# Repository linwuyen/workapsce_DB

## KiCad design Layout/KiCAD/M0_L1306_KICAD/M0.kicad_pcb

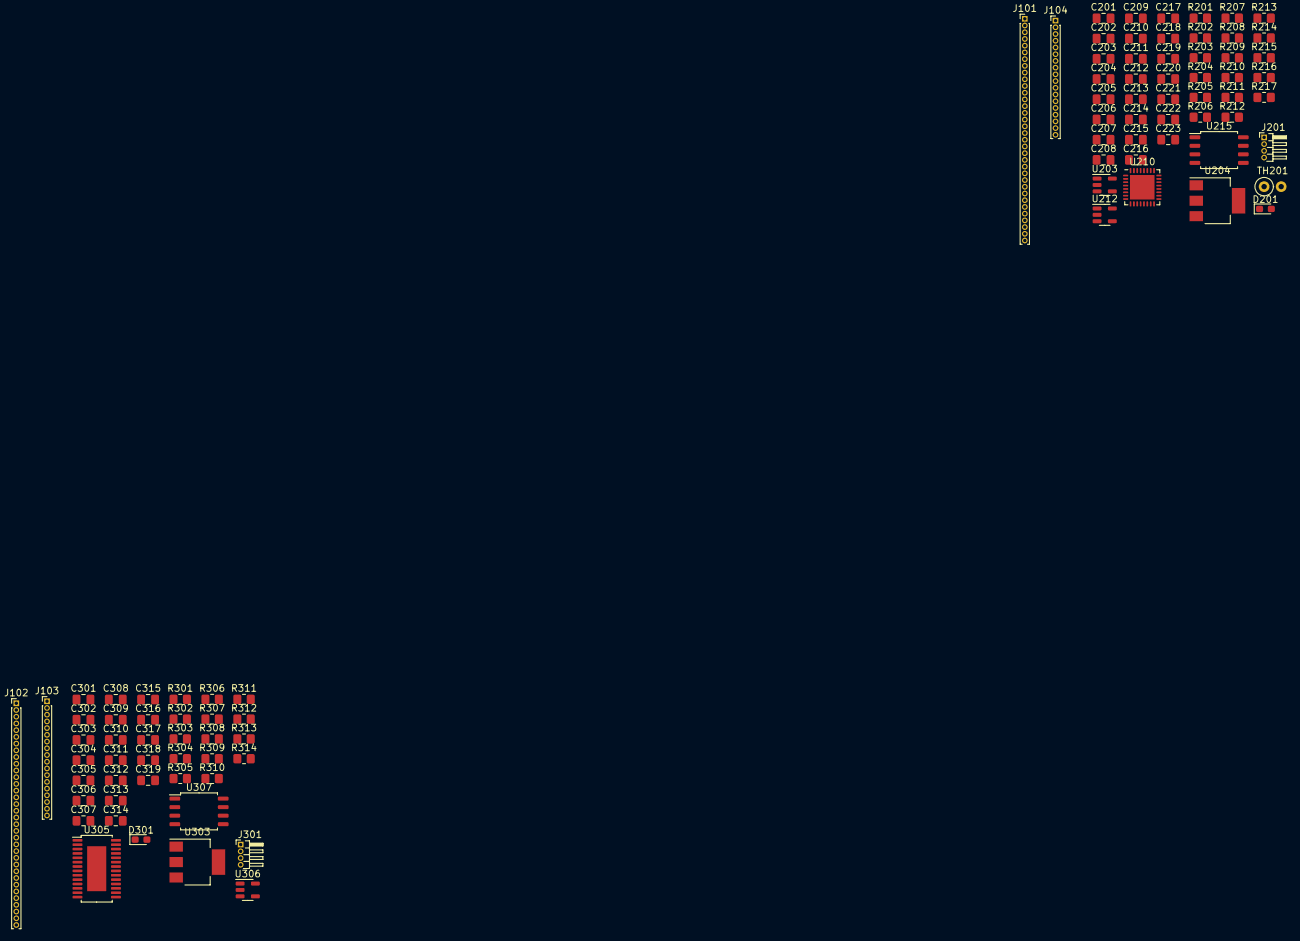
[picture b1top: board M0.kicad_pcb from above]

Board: 2 copper layers, 91 parts (0 on the bottom side), 93 nets, no tracks yet.

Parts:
C201, C207, C218, C219, C221, C304, C311, C312, C318: 10nF; C_0805_2012Metric_Pad1.18x1.45mm_HandSolder
C202, C203, C301, C303: 4.7uF; C_0805_2012Metric_Pad1.18x1.45mm_HandSolder
C204, C216, C319: 0.47uF; C_0805_2012Metric_Pad1.18x1.45mm_HandSolder
C205, C210, C213, C217, C220, C223, C305, C306, C310, C315, C317: 100nF; C_0805_2012Metric_Pad1.18x1.45mm_HandSolder
C206, C209, C211, C222, C302, C307, C308, C316: 100pF; C_0805_2012Metric_Pad1.18x1.45mm_HandSolder
C208, C212, C309: 10uF; C_0805_2012Metric_Pad1.18x1.45mm_HandSolder
C214, C215, C313, C314: 18pF; C_0805_2012Metric_Pad1.18x1.45mm_HandSolder
D201, D301: LED; LED_0603_1608Metric_Pad1.05x0.95mm_HandSolder
J101, J102: Conn_01x34_Socket; PinHeader_1x34_P1.00mm_Vertical
J103, J104: Conn_01x18_Pin; PinHeader_1x18_P1.00mm_Vertical
J201, J301: SWD_01x04_Pin; PinHeader_1x04_P1.00mm_Horizontal
R201, R214, R311: 4.7k; R_0805_2012Metric_Pad1.20x1.40mm_HandSolder
R202, R203, R207, R208, R209, R302, R303, R307, R313, R314: 22R; R_0805_2012Metric_Pad1.20x1.40mm_HandSolder
R204, R205, R216, R301, R304: 10k; R_0805_2012Metric_Pad1.20x1.40mm_HandSolder
R206, R210, R211, R305, R309, R310: 2.2k; R_0805_2012Metric_Pad1.20x1.40mm_HandSolder
R212: 100k; R_0805_2012Metric_Pad1.20x1.40mm_HandSolder
R213, R215, R306, R308: 10R; R_0805_2012Metric_Pad1.20x1.40mm_HandSolder
R217, R312: 100R; R_0805_2012Metric_Pad1.20x1.40mm_HandSolder
TH201: Thermistor_NTC_5K; R_Axial_DIN0207_L6.3mm_D2.5mm_P2.54mm_Vertical
U203, U212, U306: SN74LVC1G08; SOT-23-5
U204, U303: LM1117MP-3.3; SOT-223-3_TabPin2
U210: MSPM0L1306; QFN-32-1EP_5x5mm_P0.5mm_EP3.65x3.65mm
U215, U307: TL082; SOIC-8_5.275x5.275mm_P1.27mm
U305: M0A23EC1AC; TSSOP-28-1EP_4.4x9.7mm_P0.65mm_EP2.85x6.7mm

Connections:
+3.3V: C306.1, C309.1, C310.1, C315.2, C317.2, C319.1, J301.1, R301.1, U303.2 (VO), U305.1 (VDD), U306.5 (VCC), U307.8 (V+)
+3.3VP: C204.1, C208.1, C210.1, C212.1, C213.1, C217.1, C220.1, C223.1, J201.1, R204.2, R205.1, R206.1, R210.1, R211.1, R216.1, U203.5 (VCC), U204.2 (VO), U210.4 (VDD), U212.5 (VCC), U215.8 (V+)
/Nunoton_M0A23EC1AC/5V: C301.1, C303.1, C305.1, U303.3 (VI)
/Nunoton_M0A23EC1AC/ACMP0: J103.4, U305.23 (PC.1)
/Nunoton_M0A23EC1AC/ADC12: J103.5, R312.1
/Nunoton_M0A23EC1AC/DAC 1: C318.1, J103.3, R311.1
/Nunoton_M0A23EC1AC/GND: C301.2, C303.2, C305.2, C309.2, C310.2, U303.1 (GND)
/Nunoton_M0A23EC1AC/MCU_TX: C312.1, R308.2
/Nunoton_M0A23EC1AC/PD.1: J103.10, U305.9 (PD.1)
/Nunoton_M0A23EC1AC/PD.2: J103.11, U305.10 (PD.2)
/Nunoton_M0A23EC1AC/PD.3: J103.12, U305.11 (PD.3)
/Nunoton_M0A23EC1AC/PD.5: J103.13, U305.18 (PD.5)
/Nunoton_M0A23EC1AC/PD.6: U305.19 (PD.6), U305.20 (PD.7)
/Nunoton_M0A23EC1AC/PICO: C308.1, R307.2
/Nunoton_M0A23EC1AC/POCI: C307.1, R303.2
/Nunoton_M0A23EC1AC/PWM_BRAKE1: J103.2, U305.25 (PA.2)
/Nunoton_M0A23EC1AC/PWM_CH0: J103.1, R311.2, U306.4
/Nunoton_M0A23EC1AC/SCL: C313.1, R309.2, U305.14 (PB.7)
/Nunoton_M0A23EC1AC/SCLK: C302.1, R302.2
/Nunoton_M0A23EC1AC/SDA: C314.1, R310.2, U305.16 (PB.5)
/Nunoton_M0A23EC1AC/TM0: J103.8, U305.17 (PD.4)
/Nunoton_M0A23EC1AC/TM0_EXT: J103.7, U305.22 (PC.2)
/TI_MSPM0L1306/+5VP: C202.1, C203.1, C205.1, U204.3 (VI)
/TI_MSPM0L1306/ADC12: J104.12, R217.1
/TI_MSPM0L1306/CAPTURE_0: J104.3, U210.11 (PA7)
/TI_MSPM0L1306/COMPARE_0: J104.4, U210.9 (PA5)
/TI_MSPM0L1306/DAC 1: C201.1, J104.6, R201.2
/TI_MSPM0L1306/DAC 2: C219.1, J104.10, R214.1
/TI_MSPM0L1306/GND: C202.2, C203.2, C205.2, C208.2, C210.2, U204.1 (GND)
/TI_MSPM0L1306/OPA1.IN0+: J104.8, R216.2, TH201.1, U210.22 (PA18/A7)
/TI_MSPM0L1306/OPA1.IN1-: J104.7, U210.21 (PA17)
/TI_MSPM0L1306/OPA1.OUT: J104.9, U210.20 (PA16/A8)
/TI_MSPM0L1306/PA1: J104.13, U210.2 (PA1)
/TI_MSPM0L1306/PA12: J104.14, U210.16 (PA12)
/TI_MSPM0L1306/PA13: J104.15, U210.17 (PA13)
/TI_MSPM0L1306/PA14: J104.16, U210.18 (PA14)
/TI_MSPM0L1306/PA15: J104.17, U210.19 (PA15/A9)
/TI_MSPM0L1306/PA24: J104.18, U210.28 (PA24/A3)
/TI_MSPM0L1306/PICO: C211.1, R209.2
/TI_MSPM0L1306/POCI: C206.1, R207.2
/TI_MSPM0L1306/PWM 1: J104.5, R201.1, U203.4
/TI_MSPM0L1306/PWM 2: J104.11, R214.2, U212.4
/TI_MSPM0L1306/SCL: C215.1, R211.2, U210.15 (PA11)
/TI_MSPM0L1306/SCLK: C209.1, R208.2
/TI_MSPM0L1306/SDA: C214.1, R210.2, U210.14 (PA10)
/TI_MSPM0L1306/TX: C218.1, R213.1
/TI_MSPM0L1306/VREF+: J104.1, U210.27 (PA23/VREF+)
/TI_MSPM0L1306/VREF-: J104.2, U210.25 (PA21/A5/VREF-)
unnamed: D201.2 (A), R206.2
unnamed: D201.1 (K), R205.2, U210.1 (PA0)
unnamed: D301.2 (A), R305.2
unnamed: D301.1 (K), R304.2, U305.3 (PA.4)
unnamed: J103.6, J103.9, J103.14, J103.15, J103.16, J103.17, J103.18
unnamed: J201.2, R202.2
unnamed: J201.3, R203.2
unnamed: C204.2, J201.4
unnamed: J301.2, R313.1
unnamed: J301.3, R314.1
unnamed: C316.2, C318.2, C319.2, J301.4
unnamed: C217.2, C220.2, U203.3 (GND), U212.3 (GND)
unnamed: C206.2, C209.2, C211.2, C214.2, C215.2
unnamed: C212.2, C213.2, C216.2, U210.5 (VSS)
unnamed: C207.1, R204.1, U210.3 (NRST)
unnamed: R212.1, U210.6 (PA2/ROSC)
unnamed: U203.1, U203.2, U210.7 (PA3)
unnamed: R207.1, U210.8 (PA4)
unnamed: R208.1, U210.10 (PA6)
unnamed: R209.1, U210.13 (PA9)
unnamed: R203.1, U210.23 (PA19/SWDIO)
unnamed: R202.1, U210.24 (PA20/SWCLK/A6)
unnamed: U210.26 (PA22/A4), U212.1, U212.2
unnamed: R213.2, U210.29 (PA25/A2)
unnamed: C221.1, R215.2, U210.30 (PA26/A1)
unnamed: U210.31 (PA27/A0), U215.1, U215.2 (-)
unnamed: C216.1, U210.32 (VCORE)
unnamed: C218.2, C221.2, C222.2
unnamed: C222.1, R217.2, U215.3 (+)
unnamed: C223.2, U215.4 (V-)
unnamed: C302.2, C307.2, C308.2, C311.2, C312.2, C313.2, C314.2
unnamed: C304.2, C306.2, U305.28 (VSS)
unnamed: R313.2, U305.27 (PA.0/ICE_DAT)
unnamed: R314.2, U305.26 (PA.1/_ICE_CLK)
unnamed: C304.1, R301.2, R304.1, R305.1, R309.1, R310.1, U305.4 (PA.3/_nRESET)
unnamed: U305.2 (PA.5), U307.1, U307.2 (-)
unnamed: R308.1, U305.21 (PB.4/MCU_TX)
unnamed: C311.1, R306.1, U305.15 (PB.6/MCU_RX)
unnamed: U305.24 (PC.0), U306.1, U306.2
unnamed: R303.1, U305.7 (PC.3)
unnamed: R307.1, U305.6 (PC.4)
unnamed: R302.1, U305.8 (PD.0)
unnamed: C317.1, U306.3 (GND)
unnamed: C316.1, R312.2, U307.3 (+)
unnamed: C315.1, U307.4 (V-)

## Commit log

2025-11-10 update workspace database
2025-11-10 update ASR5K Remark Doc
